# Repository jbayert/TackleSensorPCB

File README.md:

# TackleSensorPCB
 Robotic Football Tackle Sensor Hardware Design created by Jon Bayert

 This is currenly under development. A very rough price will be $15-20 but depends on the number ordered. It will be sent out for assembly but will still need to be flashed.

 The current prototype design in the kicad repo looks like:

Also take a look at:

 * [The Typical Use](./docs/TypicalUse.md)
 * [The Schematic](./docs/Schematics/schematic.pdf)

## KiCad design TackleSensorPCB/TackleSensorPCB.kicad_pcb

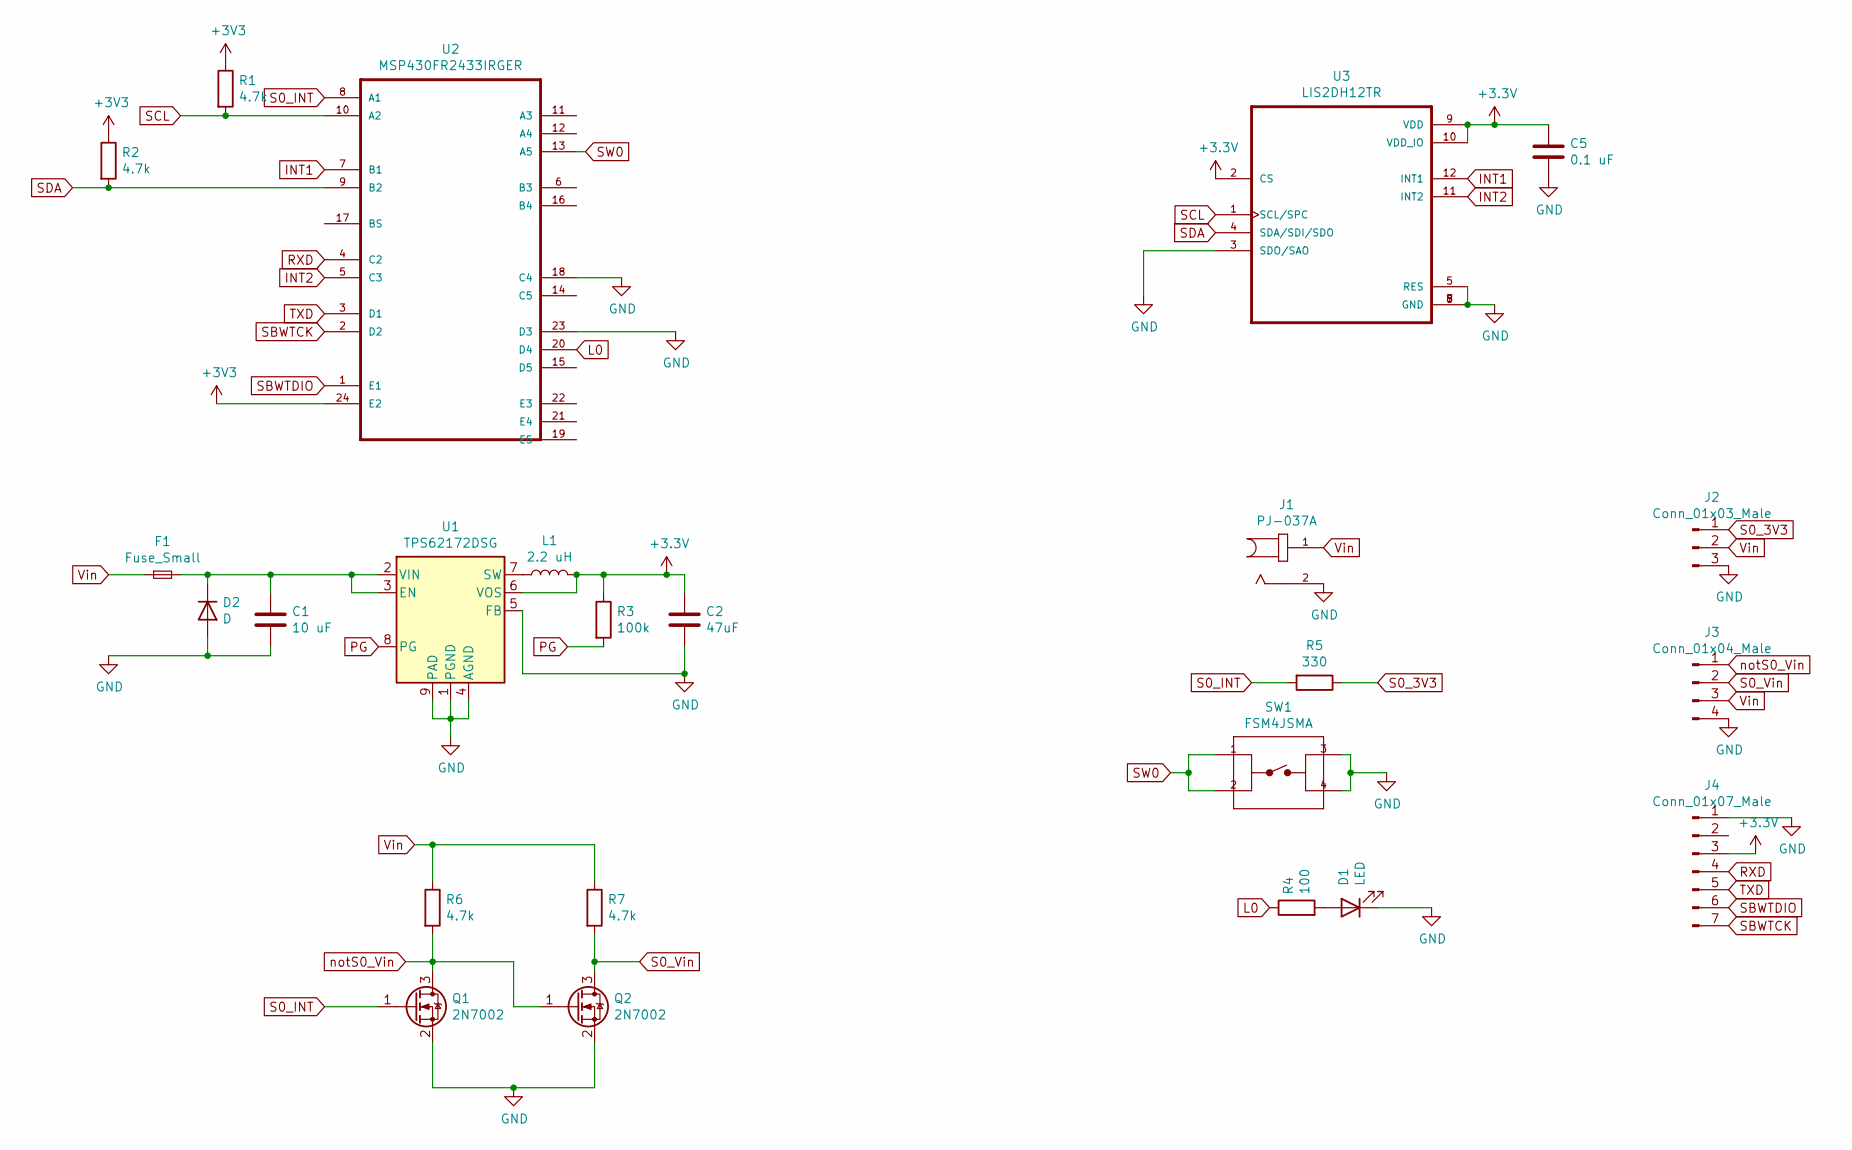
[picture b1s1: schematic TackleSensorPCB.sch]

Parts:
C1: 10 uF; C_0402_1005Metric
C2: 47uF; C_0402_1005Metric
C5: 0.1 uF; C_0402_1005Metric
D1: LED; LED_0603_1608Metric
D2: D; SOD123FL
F1: Fuse_Small; Fuse_1206_3216Metric
J1: PJ-037A; CUI_PJ-037A
J2: Conn_01x03_Male; PinHeader_1x03_P2.54mm_Vertical
J3: Conn_01x04_Male; PinHeader_1x04_P2.54mm_Vertical
J4: Conn_01x07_Male; PinHeader_1x07_P2.54mm_Vertical
L1: 2.2 uH; L_0805_2012Metric
Q1, Q2: 2N7002; SOT-23
R1, R2, R6, R7: 4.7k; R_0402_1005Metric
R3: 100k; R_0402_1005Metric
R4: 100; R_1206_3216Metric
R5: 330; R_0603_1608Metric
SW1: FSM4JSMA; TE_FSM4JSMA
U1: TPS62172DSG; WSON-8-1EP_2x2mm_P0.5mm_EP0.9x1.6mm_ThermalVias
U2: MSP430FR2433IRGER; QFN50P400X400X100-25N
U3: LIS2DH12TR; PQFN50P200X200100-12N

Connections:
GND: C1.2, C2.2, C5.2, D1.1 (K), D2.2 (A), J1.2, J2.3, J3.4, J4.1, Q1.2 (S), Q2.2 (S), SW1.3, SW1.4, U1.1 (PGND), U1.4 (AGND), U1.5 (FB), U1.9 (PAD), U2.18 (C4), U2.23 (D3), U2.25, U3.3 (SDO/SAO), U3.5 (RES), U3.6 (GND), U3.7 (GND), U3.8 (GND)
INT1: U2.7 (B1), U3.12 (INT1)
INT2: U2.5 (C3), U3.11 (INT2)
L0: R4.1, U2.20 (D4)
unnamed: C1.1, D2.1 (K), F1.2, U1.2 (VIN), U1.3 (EN)
unnamed: D1.2 (A), R4.2
unnamed: L1.1, U1.7 (SW)
PG: R3.2, U1.8 (PG)
RXD: J4.4, U2.4 (C2)
S0_3V3: J2.1, R5.1
S0_INT: Q1.1 (G), R5.2, U2.8 (A1)
S0_Vin: J3.2, Q2.3 (D), R7.2
SBWTCK: J4.7, U2.2 (D2)
SBWTDIO: J4.6, U2.1 (E1)
SCL: R1.2, U2.10 (A2), U3.1 (SCL/SPC)
SDA: R2.2, U2.9 (B2), U3.4 (SDA/SDI/SDO)
SW0: SW1.1, SW1.2, U2.13 (A5)
TXD: J4.5, U2.3 (D1)
Vin: F1.1, J1.1, J2.2, J3.3, R6.1, R7.1
notS0_Vin: J3.1, Q1.3 (D), Q2.1 (G), R6.2

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
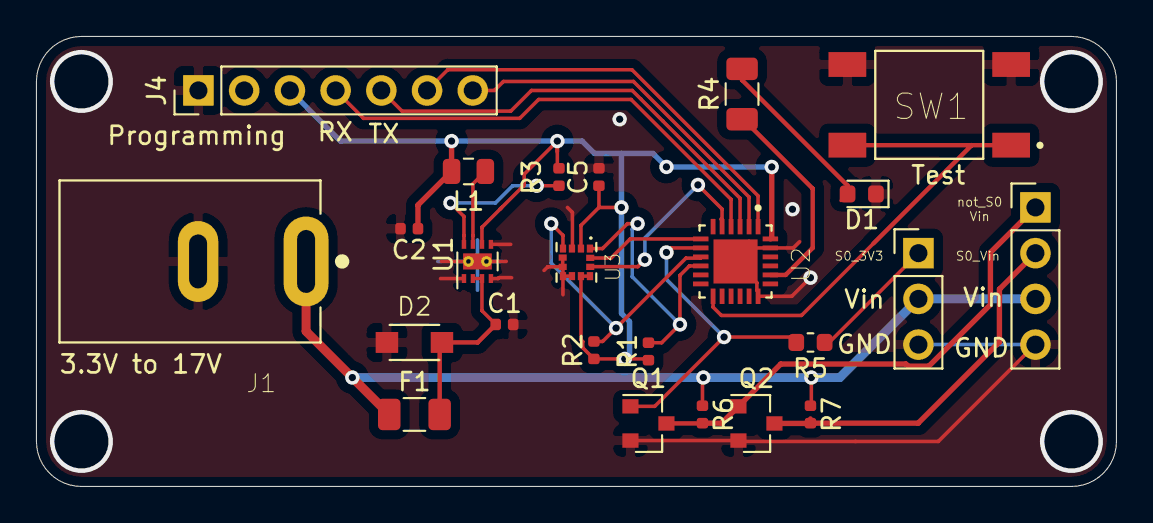
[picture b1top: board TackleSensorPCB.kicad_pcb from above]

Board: 2 copper layers, 60.0 x 25.0 mm, 24 parts (0 on the bottom side), 21 nets.

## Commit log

2020-10-12 Added pull up resistor values
2020-10-12 Added Fuse
2020-10-13 Added Documentation
    Fix the pull up resistors. They were on interrupts not i2c.
    Add not_S0_Vin pin.
    Add TypicalUse.md
    Add schematic.pdf
    Add SMT BOM
    Add pinout excel sheet
2020-10-13 Update TypicalUse.md
    Fix typo
2020-10-14 Added Footprints
2020-10-18 Created First Revision of PCB
2020-10-19 Updated to LS2
2020-10-20 Completed 3D model
2020-10-21 Updated the schematic
2021-02-10 Updated BOM
2021-11-14 Create LISCENSE
